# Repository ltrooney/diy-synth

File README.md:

# diy-synth

A repository containing a handfaul of utilities for my DIY Eurorack-based modular synthesizer. Snippets include a virtual wavetable oscillator, a step sequencer, and more...

Other (private) designs not featured include core analog synthesizer circuitry for sound generation, mixing, filtering, and envelope generation.

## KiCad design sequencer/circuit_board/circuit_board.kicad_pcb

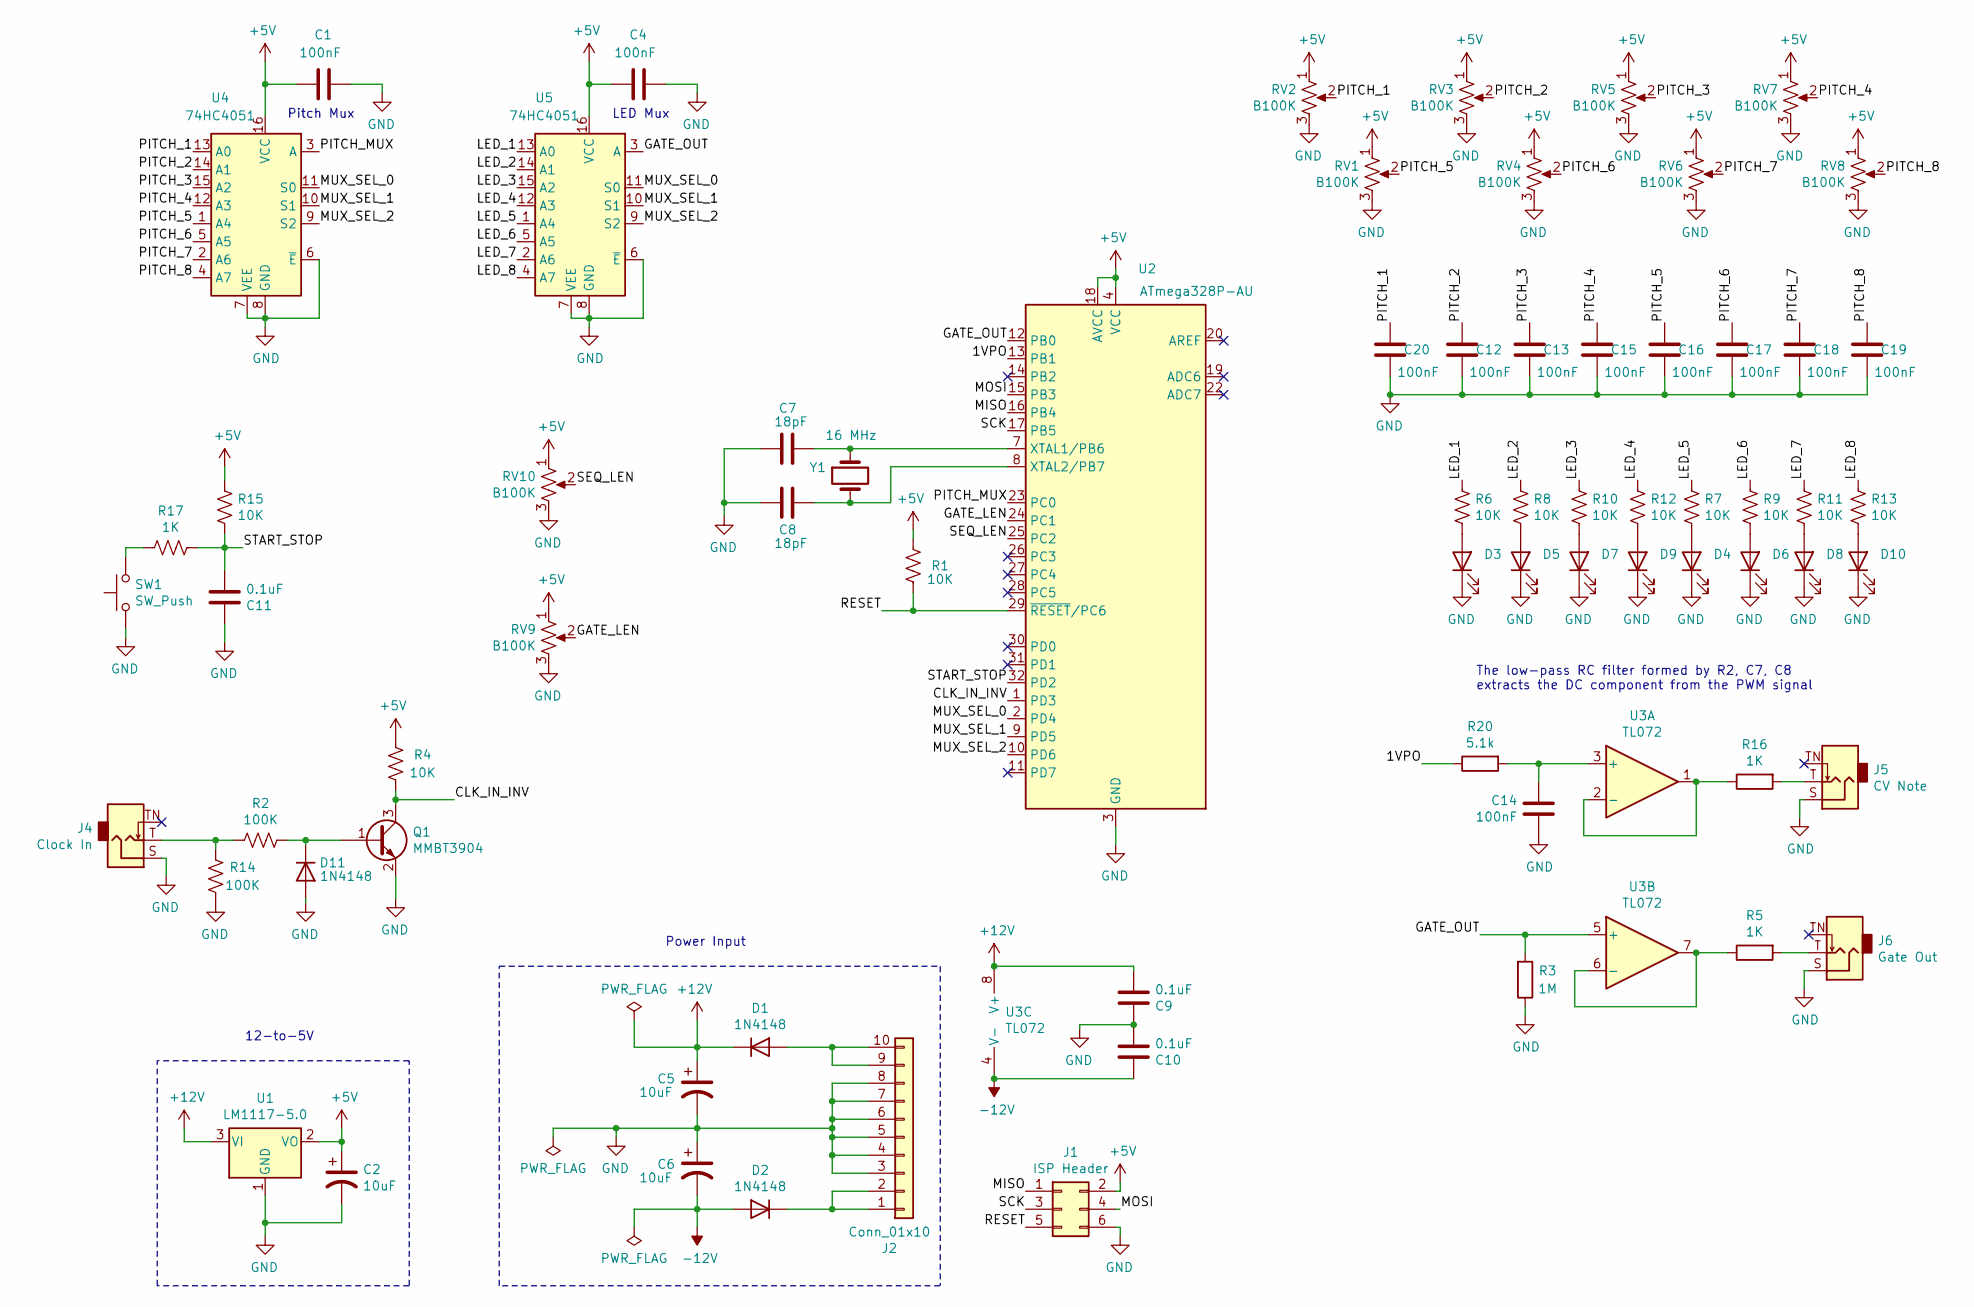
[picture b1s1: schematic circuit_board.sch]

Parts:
C1, C4, C12, C13, C14, C15, C16, C17, C18, C19, C20: 100nF; C_0805_HandSoldering
C2, C5, C6: 10uF; CP_Elec_5x5.3
C7, C8: 18pF; C_0805_HandSoldering
C9, C10, C11: 0.1uF; C_0805_HandSoldering
D1, D2, D11: 1N4148; D_SOD-123
D3: Step 1 LED; LED_D5.0mm
D4: Step 5 LED; LED_D5.0mm
D5: Step 2 LED; LED_D5.0mm
D6: Step 6 LED; LED_D5.0mm
D7: Step 3 LED; LED_D5.0mm
D8: Step 7 LED; LED_D5.0mm
D9: Step 4 LED; LED_D5.0mm
D10: Step 8 LED; LED_D5.0mm
J1: ISP Header; PinHeader_2x03_P2.54mm_Vertical
J2: Conn_01x10; IDC-Header_2x05_P2.54mm_Vertical
J4: Clock In; Jack_3.5mm_QingPu_WQP-PJ398SM_Vertical_CircularHoles
J5: CV Note; Jack_3.5mm_QingPu_WQP-PJ398SM_Vertical_CircularHoles
J6: Gate Out; Jack_3.5mm_QingPu_WQP-PJ398SM_Vertical_CircularHoles
Q1: MMBT3904; SOT-23_Handsoldering
R1, R4, R6, R7, R8, R9, R10, R11, R12, R13, R15: 10K; R_0805_HandSoldering
R2, R14: 100K; R_0805_HandSoldering
R3: 1M; R_0805_HandSoldering
R5, R16, R17: 1K; R_0805_HandSoldering
R20: 5.1k; R_0805_HandSoldering
RV1, RV2, RV3, RV4, RV5, RV6, RV7, RV8, RV9, RV10: B100K; Potentiometer_Alpha_RD901F-40-00D_Single_Vertical
SW1: SW_Push; SW_PUSH_6mm
U1: LM1117-5.0; SOT-223-3_TabPin2
U2: ATmega328P-AU; TQFP-32_7x7mm_Pitch0.8mm
U3: TL072; SOIC-8_3.9x4.9mm_Pitch1.27mm
U4, U5: 74HC4051; SOIC-16_3.9x9.9mm_Pitch1.27mm
Y1: 16 MHz; Crystal_SMD_HC49-SD_HandSoldering

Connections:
+5V: C1.1, C2.1, C4.1, J1.2, R1.2, R4.2, R15.1, RV1.1, RV2.1, RV3.1, RV4.1, RV5.1, RV6.1, RV7.1, RV8.1, RV9.1, RV10.1, U1.2 (VO), U2.4 (VCC), U2.6 (VCC), U2.18 (AVCC), U4.16 (VCC), U5.16 (VCC)
+12V: C5.1, C9.2, D1.1 (K), U1.3 (VI), U3.8 (V+)
-12V: C6.2, C10.1, D2.2 (A), U3.4 (V-)
/1VPO: R20.1, U2.13 (PB1)
/CLK_IN_INV: Q1.3 (C), R4.1, U2.1 (PD3)
/GATE_LEN: RV9.2, U2.24 (PC1)
/GATE_OUT: R3.2, U2.12 (PB0), U3.5 (+), U5.3 (A)
/LED_1: R6.1, U5.13 (A0)
/LED_2: R8.1, U5.14 (A1)
/LED_3: R10.1, U5.15 (A2)
/LED_4: R12.1, U5.12 (A3)
/LED_5: R7.1, U5.1 (A4)
/LED_6: R9.1, U5.5 (A5)
/LED_7: R11.1, U5.2 (A6)
/LED_8: R13.1, U5.4 (A7)
/MISO: J1.1, U2.16 (PB4)
/MOSI: J1.4, U2.15 (PB3)
/MUX_SEL_0: U2.2 (PD4), U4.11 (S0), U5.11 (S0)
/MUX_SEL_1: U2.9 (PD5), U4.10 (S1), U5.10 (S1)
/MUX_SEL_2: U2.10 (PD6), U4.9 (S2), U5.9 (S2)
/PITCH_1: C20.1, RV2.2, U4.13 (A0)
/PITCH_2: C12.1, RV3.2, U4.14 (A1)
/PITCH_3: C13.1, RV5.2, U4.15 (A2)
/PITCH_4: C15.1, RV7.2, U4.12 (A3)
/PITCH_5: C16.1, RV1.2, U4.1 (A4)
/PITCH_6: C17.1, RV4.2, U4.5 (A5)
/PITCH_7: C18.1, RV6.2, U4.2 (A6)
/PITCH_8: C19.1, RV8.2, U4.4 (A7)
/PITCH_MUX: U2.23 (PC0), U4.3 (A)
/RESET: J1.5, R1.1, U2.29 (~RESET~/PC6)
/SCK: J1.3, U2.17 (PB5)
/SEQ_LEN: RV10.2, U2.25 (PC2)
/START_STOP: C11.2, R15.2, R17.1, U2.32 (PD2)
GND: C1.2, C2.2, C4.2, C5.2, C6.1, C7.1, C8.1, C9.1, C10.2, C11.1, C12.2, C13.2, C14.1, C15.2, C16.2, C17.2, C18.2, C19.2, C20.2, D3.1 (K), D4.1 (K), D5.1 (K), D6.1 (K), D7.1 (K), D8.1 (K), D9.1 (K), D10.1 (K), D11.2 (A), J1.6, J2.3, J2.4, J2.5, J2.6, J2.7, J2.8, J4.S, J5.S, J6.S, Q1.2 (E), R3.1, R14.1, RV1.3, RV2.3, RV3.3, RV4.3, RV5.3, RV6.3, RV7.3, RV8.3, RV9.3, RV10.3, SW1.1, U1.1 (GND), U2.3 (GND), U2.5 (GND), U2.21 (GND), U4.6 (~E), U4.7 (VEE), U4.8 (GND), U5.6 (~E), U5.7 (VEE), U5.8 (GND)
unnamed: C7.2, U2.7 (XTAL1/PB6), Y1.1
unnamed: C8.2, U2.8 (XTAL2/PB7), Y1.2
unnamed: C14.2, R20.2, U3.3 (+)
unnamed: D1.2 (A), J2.9, J2.10
unnamed: D2.1 (K), J2.1, J2.2
unnamed: D3.2 (A), R6.2
unnamed: D4.2 (A), R7.2
unnamed: D5.2 (A), R8.2
unnamed: D6.2 (A), R9.2
unnamed: D7.2 (A), R10.2
unnamed: D8.2 (A), R11.2
unnamed: D9.2 (A), R12.2
unnamed: D10.2 (A), R13.2
unnamed: D11.1 (K), Q1.1 (B), R2.1
unnamed: J4.T, R2.2, R14.2
unnamed: J5.T, R16.2
unnamed: J6.T, R5.2
unnamed: R5.1, U3.6 (-), U3.7
unnamed: R16.1, U3.1, U3.2 (-)
unnamed: R17.2, SW1.2

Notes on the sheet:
Power Input
12-to-5V
The low-pass RC filter formed by R2, C7, C8 extracts the DC component from the PWM signal
Pitch Mux
LED Mux

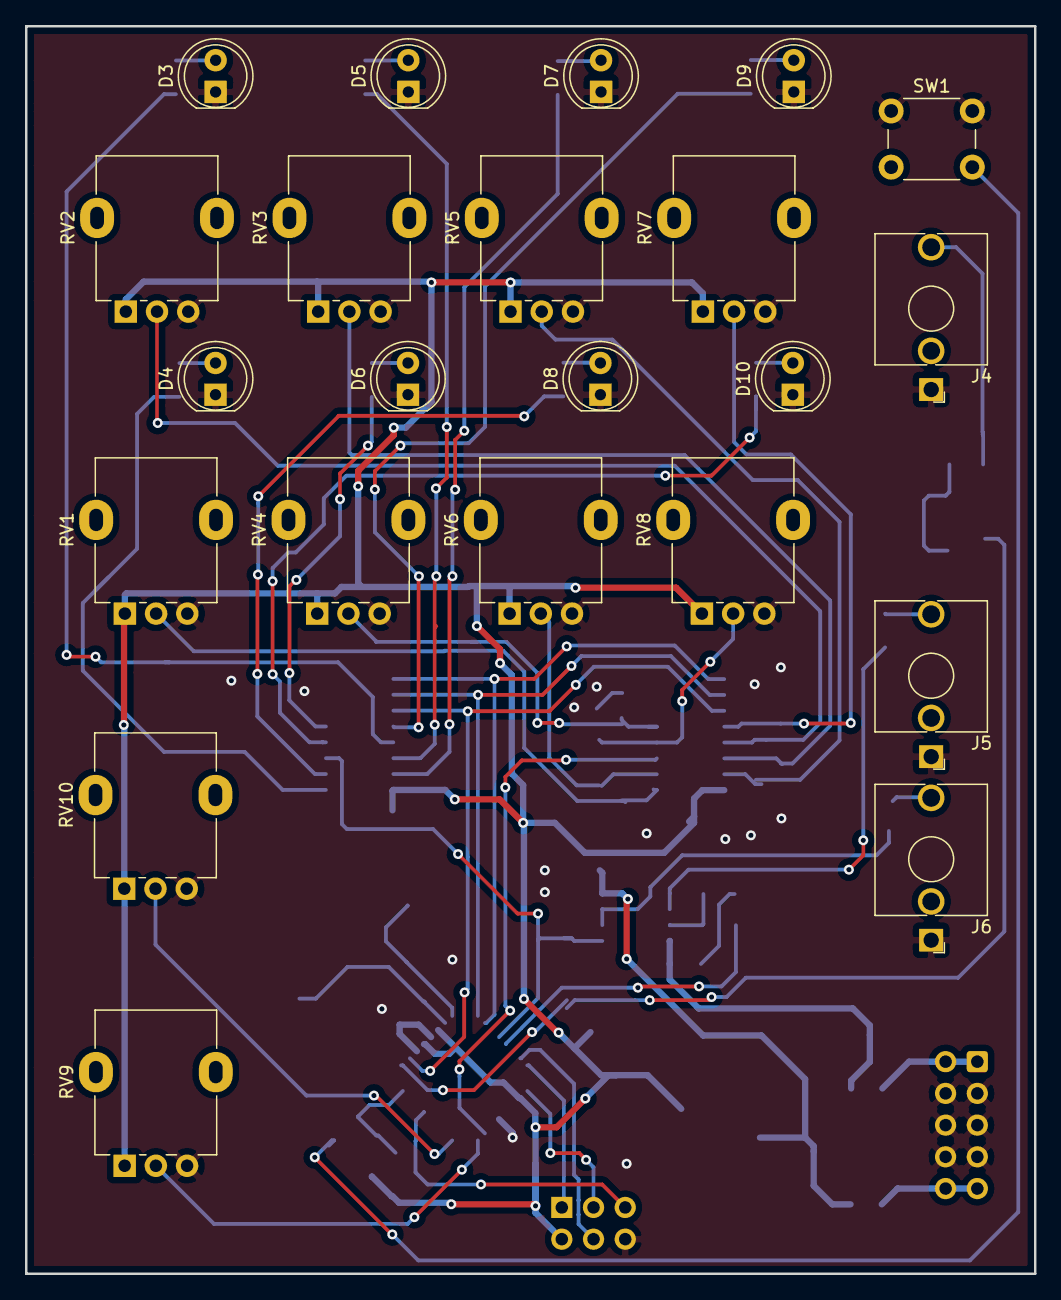
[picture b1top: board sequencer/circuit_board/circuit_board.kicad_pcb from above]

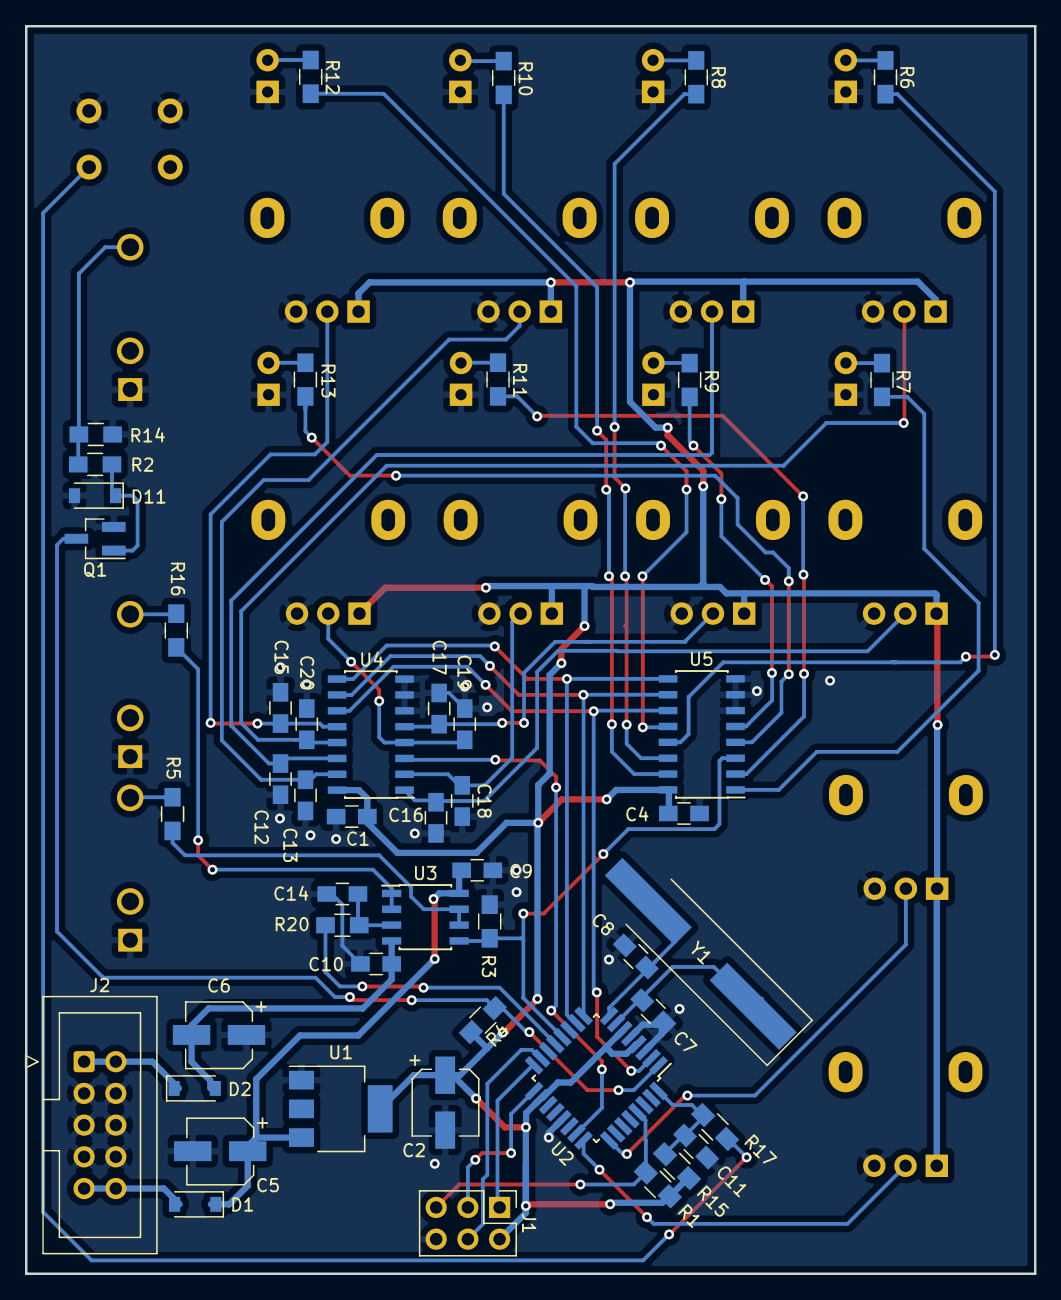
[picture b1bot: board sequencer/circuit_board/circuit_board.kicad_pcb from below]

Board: 2 copper layers, 80.8 x 99.9 mm, 71 parts (49 on the bottom side), 54 nets.

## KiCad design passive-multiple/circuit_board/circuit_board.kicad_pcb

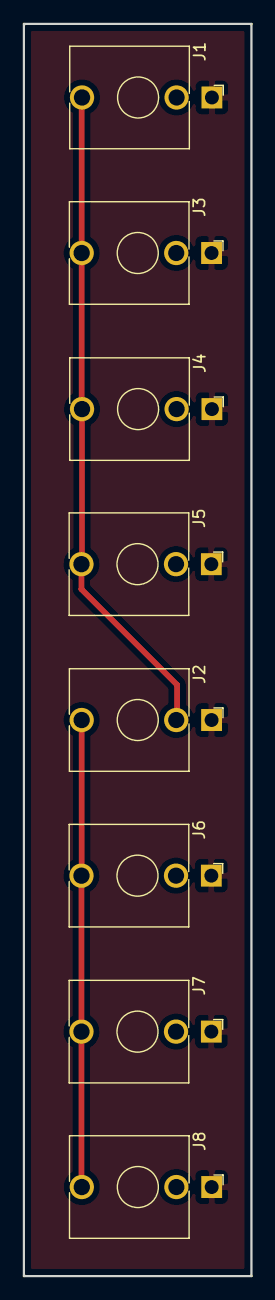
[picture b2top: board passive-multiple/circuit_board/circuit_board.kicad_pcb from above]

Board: 2 copper layers, 20.0 x 109.9 mm, 8 parts (0 on the bottom side), 3 nets.

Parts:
J1: in 1; Jack_3.5mm_QingPu_WQP-PJ398SM_Vertical_CircularHoles
J2: in 2; Jack_3.5mm_QingPu_WQP-PJ398SM_Vertical_CircularHoles
J3: out 1; Jack_3.5mm_QingPu_WQP-PJ398SM_Vertical_CircularHoles
J4: out 2; Jack_3.5mm_QingPu_WQP-PJ398SM_Vertical_CircularHoles
J5: out 3; Jack_3.5mm_QingPu_WQP-PJ398SM_Vertical_CircularHoles
J6: out 4; Jack_3.5mm_QingPu_WQP-PJ398SM_Vertical_CircularHoles
J7: out 5; Jack_3.5mm_QingPu_WQP-PJ398SM_Vertical_CircularHoles
J8: out 6; Jack_3.5mm_QingPu_WQP-PJ398SM_Vertical_CircularHoles

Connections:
GND: J1.S, J2.S, J3.S, J4.S, J5.S, J6.S, J7.S, J8.S
unnamed: J1.T, J2.TN, J3.T, J4.T, J5.T
unnamed: J2.T, J6.T, J7.T, J8.T

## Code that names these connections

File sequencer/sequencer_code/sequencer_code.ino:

#include <math.h>

/* CONSTANTS */

// pinouts
#define PIN_STRT_STP 2
#define PIN_CLK_IN_INV 3
#define PIN_MUX_SEL_0 4
#define PIN_MUX_SEL_1 5
#define PIN_MUX_SEL_2 6
#define PIN_GATE_OUT 8
#define PIN_1VPO_OUT 9
#define PIN_PITCH_MUX A0
#define PIN_GATE_LEN_POT A1
#define PIN_SEQ_LEN_POT A2

// conversion factors
const int AV_TO_DUTY_CYCLE_FACTOR = 51; // factor needed to convert AV from range [0,5] to duty cycle range [0,255]
const float ONE_STEP_VOLT = 1 / 12.0;     // the voltage difference between notes
const int MAX_STEPS = 8;

/* Serial Monitor debugging mode, active when uncommented */
//#define SERMON_DEBUG // the serial monitor will be activated when SERMON_DEBUG is defined

/* VARIABLES */
volatile unsigned long clk_period_strt;           // time (in millis since program start) that the current clock period started
volatile unsigned long last_clk_period_strt;      // time the previous clock period started, used to determine clock frequency
float clk_period;              // clock period (in millis)
uint16_t step_time_elapsed;    // time (in millis) that the current step has been playing for
bool last_iter_gate_high;      // determines if gate was high in the last iteration; used to avoid excessive calls to digitalWrite()
unsigned long step_cnt;        // number of steps elapsed since start of program
volatile bool new_step;        // becomes active if the step transitions in the current loop iteration
volatile bool stop_stepping;   // flag to indicate if the sequencer should stop sequencing; controlled by the start/stop button
int num_steps;                 // number of steps in the sequence


void setup() {

#ifdef SERMON_DEBUG
  Serial.begin(9600);
#endif

  pinMode(PIN_MUX_SEL_0, OUTPUT);
  pinMode(PIN_MUX_SEL_1, OUTPUT);
  pinMode(PIN_MUX_SEL_2, OUTPUT);
  pinMode(PIN_GATE_OUT, OUTPUT);
  pinMode(PIN_1VPO_OUT, OUTPUT);
  pinMode(PIN_STRT_STP, INPUT);
  pinMode(PIN_CLK_IN_INV, INPUT);

  attachInterrupt(digitalPinToInterrupt(PIN_STRT_STP), start_stop_handle, FALLING);
  attachInterrupt(digitalPinToInterrupt(PIN_CLK_IN_INV), clk_handle, FALLING);

  // initiliaze variables
  clk_period_strt = 0;
  last_clk_period_strt = 0;
  step_time_elapsed = 0;
  clk_period = 0;
  step_cnt = 0;
  new_step = false;
  last_iter_gate_high = false;
  stop_stepping = false;

  // set pin 9 PWM frequency to ~31kHz so DAC low-pass is more precise
  TCCR1B = TCCR1B & B11111000 | B00000001;
}

void loop() {
  // Wait if "stop" button pressed or haven't received clock trigger yet
  while (stop_stepping || (last_clk_period_strt == 0));

  // determine clock period
  clk_period = clk_period_strt - last_clk_period_strt;

  if (new_step) {

    new_step = false;

    /* DETERMINE STEP NUMBER */
    float seq_len_v = get_wiper_voltage(PIN_SEQ_LEN_POT);
    seq_len_v *= (7.0 / 5); // convert range from [0,5] to [0,7]
    num_steps = ((int) seq_len_v) + 1;

    if (num_steps > MAX_STEPS) {
      num_steps = MAX_STEPS;
    }

    uint8_t step_num = step_cnt % num_steps;
    step_cnt++;
        
    /* READ PITCH POTS */
    // set up the mux
    byte s0 = step_num & 0x01;
    byte s1 = (step_num >> 1) & 0x01;
    byte s2 = (step_num >> 2) & 0x01;
    digitalWrite(PIN_MUX_SEL_0, s0);
    digitalWrite(PIN_MUX_SEL_1, s1);
    digitalWrite(PIN_MUX_SEL_2, s2);
    float pitch_v = get_wiper_voltage(PIN_PITCH_MUX);

    /* QUANTIZE PITCH */
    pitch_v = ONE_STEP_VOLT * floor(pitch_v / ONE_STEP_VOLT);
  
    /* SEND PITCH OUT */
    analogWrite(PIN_1VPO_OUT, av_to_duty_cycle(pitch_v));
     
    /* SEND GATE OUT */
    set_gate(true);
  }

  /* READ GATE LENGTH POT */
  float gate_len_v = get_wiper_voltage(PIN_GATE_LEN_POT);
  float gate_duty_cycle = gate_len_v * 20;  // convert range from [0,5] to [0,100]
  float gate_dur = clk_period * (gate_duty_cycle / 100);

  // Determine if step has been activated longer than the gate length
  step_time_elapsed = millis() - clk_period_strt;
  if ((step_time_elapsed > gate_dur) && last_iter_gate_high) { 
    set_gate(false);
  }  

  delay(10);
}

/**********************************/
/*          HELPERS               */
/**********************************/

/* Reads the voltage at analog pin 'pin_name' */
float get_wiper_voltage(int pin) {
  int val = analogRead(pin);
  val = 1023 - val;   // invert due to inverted pots
  return val / 204.6; // convert range from [0,1023] to [0,5]
}

/* Convert a 1V/octave analog voltage to a PWM duty cycle */
int av_to_duty_cycle(float av) {
  return (int) (av * AV_TO_DUTY_CYCLE_FACTOR);
}

void set_gate(bool hi_lo) {
  digitalWrite(PIN_GATE_OUT, hi_lo);
  last_iter_gate_high = hi_lo;
}

/**********************************/
/*            ISRs                */
/**********************************/
void start_stop_handle() {
  static unsigned long last_press_time = 0;
  unsigned long curr_int_time = millis();
  if (curr_int_time - last_press_time > 200) {  // avoid switch debounce
    stop_stepping = !stop_stepping;
    if (stop_stepping) {
      set_gate(false);
    }
  }
  last_press_time = curr_int_time;
}

void clk_handle() {
  last_clk_period_strt = clk_period_strt;
  clk_period_strt = millis();
  new_step = true;
}

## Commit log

2021-04-19 initial commit of public files
2021-04-26 ported to jupyter-lab
2021-04-26 changed folder name to vclfo
2021-04-30 refactored ipython; initialized stm32 project and added wavetable_init/free
2021-05-02 wrote wavetable initialization code
2021-05-04 modified python wavetable sample code to make it work with 1d compressed array instead of 3d array
2021-05-04 removed wavetable gen code from vclfo.ipynb; added octave and # wave info to wavetable_init.dat header
2021-05-04 moved meta to a different file due C compatibility
2021-05-07 optimized wt_sample(); reduced execution time from 42us to 8us
2021-05-14 generated code for SPI2 with DMA
2021-08-15 split code out of main.c
2021-08-16 resolved errors; save before auto-code regeneration
2021-08-19 working TIM1 and SPI clock output
2021-08-21 SPI transmission working with dummy values
2021-08-21 refactored some DAC code
2021-08-28 working ADC with manual DMA request each conversion
2021-09-05 put custom drivers into own directory; refactored DAC code; updated master clock from 84 MHz to 96 MHz
2021-09-06 wrote engine.c and refactored DAC_Init()
2021-09-09 refactored ipython simulation code
2021-09-09 refactored CV classes
2021-09-09 added Playback class
2021-09-10 refactored sim by splitting Playback and Wavetable classes
2021-09-17 refactored simulation code
2021-09-18 refactored wavetable code and removed pitch morphing between tables due to aliasing effect
2021-09-18 refactored CVsim
2021-09-18 converted coarse CV from exp to linear
2021-09-19 added ability to precompute a specified number of samples per CV snapshot
2021-09-25 converted from wavetable to polyblep technique
2021-09-27 pulse width modulation with polyblep
2021-09-27 added sample calculation of square wave
2021-09-29 implemented polyblep
2021-10-12 implemented polyblep and simulated ADC conversions
2021-10-12 added noise simulation to ModuleInput
2021-10-24 save before refactor
